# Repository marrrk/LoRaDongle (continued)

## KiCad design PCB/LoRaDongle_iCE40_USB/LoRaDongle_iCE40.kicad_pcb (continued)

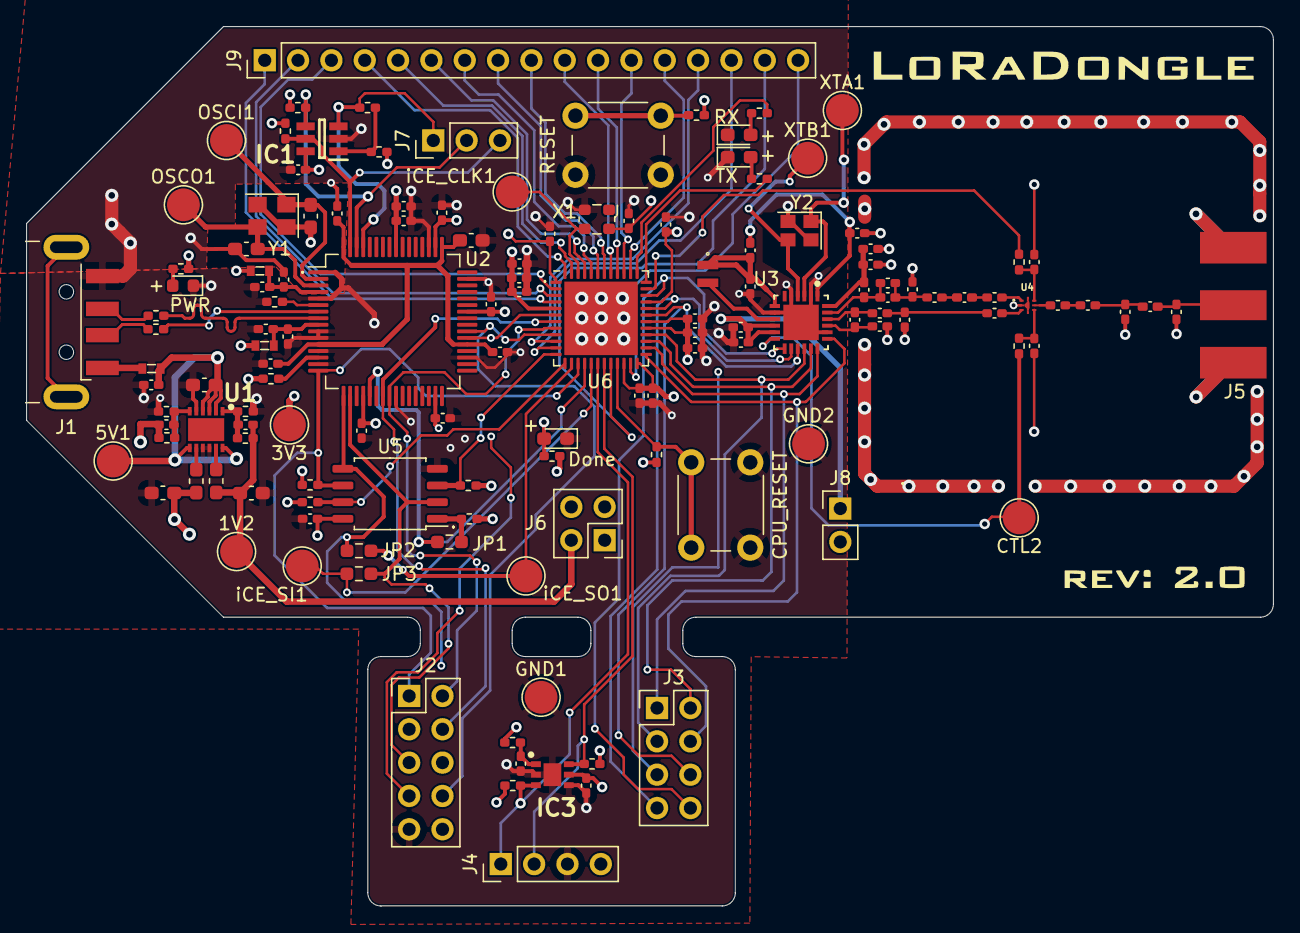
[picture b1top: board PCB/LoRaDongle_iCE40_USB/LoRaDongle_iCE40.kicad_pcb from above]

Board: 4 copper layers, 95.0 x 67.0 mm, 140 parts (1 on the bottom side), 97 nets.

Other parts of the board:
G1: LOGO; LoRaDongleLogo
G3: LOGO; mark_njoroge

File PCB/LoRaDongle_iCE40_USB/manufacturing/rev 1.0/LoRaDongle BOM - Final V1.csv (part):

Item,Qty,Reference(s),Value,Footprint,Description,Manufacturer,Manufacturer Part Number,Package,Type,Comments
1,11,"C1, C8, C9, C12, C13, C16, C18, C19, C20, C21, C22",0.1uF,Capacitor_SMD:C_0402_1005Metric_Pad0.74x0.62mm_HandSolder,CAP CER 0.1UF 16V X7R 0402,Murata Electronics,GCM155R71C104KA55J,0402,SMD,
2,3,"C2, C4, C6",10uF,Capacitor_SMD:C_0603_1608Metric_Pad1.08x0.95mm_HandSolder,CAP CER 10UF 6.3V X5R 0603,Murata Electronics,GRM188R60J106ME47D,0603,SMD,
3,3,"C3, C5, C47",22pF,Capacitor_SMD:C_0402_1005Metric_Pad0.74x0.62mm_HandSolder,CAP CER 22PF 50V C0G/NP0 0402,Murata Electronics,GRM1555C1H220FA01D,0402,SMD,
4,3,"C7, C11, C17",4.7uF,Capacitor_SMD:C_0402_1005Metric_Pad0.74x0.62mm_HandSolder,CAP CER 4.7UF 6.3V X6S 0402,Murata Electronics,GRM155C80J475MEAAD,0402,SMD,
5,2,"C10, C35",10nF,Capacitor_SMD:C_0402_1005Metric_Pad0.74x0.62mm_HandSolder,CAP CER 10000PF 50V X7R 0402,Murata Electronics,GRM155R71H103KA88J,0402,SMD,
6,2,"C14, C15",27pF,Capacitor_SMD:C_0603_1608Metric_Pad1.08x0.95mm_HandSolder,CAP CER 27PF 50V C0G/NP0 0603,Murata Electronics,GRM1885C1H270JA01D,0603,SMD,
7,10,"C23, C24, C25, C26, C27, C29, C30, C31, C32, C33",100nF,Capacitor_SMD:C_0402_1005Metric_Pad0.74x0.62mm_HandSolder,CAP CER 0.1UF 16V X7R 0402,Murata Electronics,GRM155R71C104KA88D,0402,SMD,
8,2,"C28, C34",1uF,Capacitor_SMD:C_0402_1005Metric_Pad0.74x0.62mm_HandSolder,CAP CER 1UF 6.3V X7R 0402,Murata Electronics,GRM155R70J105MA12D,0402,SMD,
9,2,"C36, C37",1.8pF,Capacitor_SMD:C_0402_1005Metric_Pad0.74x0.62mm_HandSolder,CAP CER 1.8PF 50V C0G/NP0 0402,Murata Electronics,GRM1555C1H1R8WA01D,0402,SMD,
10,1,C38,1pF,Capacitor_SMD:C_0402_1005Metric_Pad0.74x0.62mm_HandSolder,CAP CER 1PF 50V C0G/NP0 0402,Murata Electronics,GRM1555C1H1R0BA01D,0402,SMD,
11,3,"C39, C40, C44",470pF,Capacitor_SMD:C_0402_1005Metric_Pad0.74x0.62mm_HandSolder,CAP CER 470PF 50V C0G/NP0 0402,Murata Electronics,GRM1555C1H471JA01D,0402,SMD,
12,2,"C41, C43",33pF,Capacitor_SMD:C_0402_1005Metric_Pad0.74x0.62mm_HandSolder,CAP CER 33PF 50V C0G 0402,TDK Corporation,CGA2B2C0G1H330J050BA,0402,SMD,
13,1,C42,470nF,Capacitor_SMD:C_0402_1005Metric_Pad0.74x0.62mm_HandSolder,CAP CER 0.47UF 10V X5R 0402,Murata Electronics,GRM155R61A474KE15D,0402,SMD,
14,1,C45,47nF,Capacitor_SMD:C_0402_1005Metric_Pad0.74x0.62mm_HandSolder,CAP CER 0.047UF 16V X7R 0402,Murata Electronics,GRM155R71C473KA01J,0402,SMD,
15,1,C46,47pF,Capacitor_SMD:C_0402_1005Metric_Pad0.74x0.62mm_HandSolder,CAP CER 47PF 50V C0G/NP0 0402,Murata Electronics,GRM1555C1H470JA01D,0402,SMD,
16,2,"C48, C50",3.3pF,Capacitor_SMD:C_0402_1005Metric_Pad0.74x0.62mm_HandSolder,CAP CER 3.3PF 50V C0G/NP0 0402,Murata Electronics,GJM1555C1H3R3DB01D,0402,SMD,
17,1,C49,3pF,Capacitor_SMD:C_0402_1005Metric_Pad0.74x0.62mm_HandSolder,CAP CER 3PF 50V C0G/NP0 0402,Murata Electronics,GRM1555C1H3R0BA01J,0402,SMD,
18,1,C51,6.8pF,Capacitor_SMD:C_0402_1005Metric_Pad0.74x0.62mm_HandSolder,CAP CER 6.8PF 50V C0G/NP0 0402,Murata Electronics,GRM1555C1H6R8BA01D,0402,SMD,
19,1,C52,12pF,Capacitor_SMD:C_0402_1005Metric_Pad0.74x0.62mm_HandSolder,CAP CER 12PF 50V C0G/NP0 0402,Murata Electronics,GRM1555C1H120JA01J,0402,SMD,
20,1,D1,PWR,LED_SMD:LED_0805_2012Metric_Pad1.15x1.40mm_HandSolder,LED RED CLEAR CHIP SMD,SunLED,XZM2CRK54WA-8,0805,SMD,
21,1,D2,Done,LED_SMD:LED_0603_1608Metric_Pad1.05x0.95mm_HandSolder,LED GREEN CLEAR CHIP SMD,SunLED,XZVG53W-8,0603,SMD,
22,1,D3,TX,LED_SMD:LED_0603_1608Metric_Pad1.05x0.95mm_HandSolder,LED GREEN CLEAR CHIP SMD,SunLED,XZVG53W-8,0603,SMD,
23,1,D4,RX,LED_SMD:LED_0603_1608Metric_Pad1.05x0.95mm_HandSolder,LED GREEN CLEAR CHIP SMD,SunLED,XZVG53W-8,0603,SMD,
24,3,"FB1, FB2, FB3",600R/0.5A,digikey-footprints:0603,FERRITE BEAD 600 OHM 0603 1LN,Murata Electronics North America,BLM18AG601SN1D,0603,SMD,
25,1,IC1,93LC56BT-I_OT,93LC56B-I_OT_KiCad:SOT95P270X145-6N,"2K,128 X 16,Serial EE,SOT23",Microchip,93LC56BT-I/OT,SOT23-6,SMD,
26,1,IC2,ICE40UP5K-UWG30ITR1K,ICE40UP5K-UWG30ITR1K_KiCad:BGA30C40P5X6_211X254X60,"FPGA - Field Programmable Gate Array iCE40-UltraPlus, 5280 LUTs, 1.2V",Lattice Semiconductor,ICE40UP5K-UWG30ITR1K,"30-UFBGA, WLCSP",SMD,
27,1,IC3,N25Q032A13ESC40F,N25Q032A13ESC40F:SOIC127P600X175-8N,FLASH - NOR Memory IC 32Mb (8M x 4) SPI 108MHz  8-SO,"Alliance Memory, Inc.",N25Q032A13ESC40F,8-SOIC,SMD,
28,1,J1,USB_A,Connector_USB:USB_A_CNCTech_1001-011-01101_Horizontal,"USB A 2.0, R/A, SMT, PLUG",Adam Tech,USB-AP-S-RA-SMT,Plug,SMD - Through Hole,
29,1,J2,Conn_01x08,Connector_PinHeader_2.54mm:PinHeader_2x04_P2.54mm_Vertical,2x04 Male Header,-,-,-,Through Hole,
30,2,"J3, J9",Conn_02x02_Top_Bottom,Connector_PinHeader_2.54mm:PinHeader_2x02_P2.54mm_Vertical,2x02 Male Header,-,-,-,Through Hole,
31,1,J4,Jumper,Connector_PinHeader_2.54mm:PinHeader_1x03_P2.54mm_Vertical,1x03 Male Header,-,-,-,Through Hole,
32,1,J5,142-0701-801,digikey-footprints:RF_SMA_BoardEdge_142-0701-801,CONN SMA JACK STR 50OHM EDGE MNT,Cinch Connectivity Solutions Johnson,142-0701-801,Edge Connector,SMD,
33,1,J6,Conn_01x06,Connector_PinHeader_2.54mm:PinHeader_1x06_P2.54mm_Vertical,1x06 Male Header,-,-,-,Through Hole,
34,1,J7,Jumper_NC_Small,Connector_PinHeader_2.54mm:PinHeader_1x02_P2.54mm_Vertical,1x02 Male Header,-,-,-,Through Hole,
35,1,J8,Jumper,Connector_PinHeader_2.54mm:PinHeader_1x02_P2.54mm_Vertical,1x02 Male Header,-,-,-,Through Hole,
36,1,J10,Jumper_2_Open,Connector_PinHeader_2.54mm:PinHeader_1x02_P2.54mm_Vertical,1x02 Male Header,-,-,-,Through Hole,
37,2,"L1, L2",2.2uH,Inductor_SMD:L_0603_1608Metric_Pad1.05x0.95mm_HandSolder,FIXED IND 2.2UH 1.2A 292MOHM SMD,Taiyo Yuden,MCHK1608T2R2MKN,0603,SMD,
38,2,"L3, L6",47nH,Inductor_SMD:L_0402_1005Metric_Pad0.77x0.64mm_HandSolder,FIXED IND 47NH 210MA 1.08OHM SMD,Murata Electronics,LQW15AN47NJ00D,0402,SMD,
39,1,L4,18nH,Inductor_SMD:L_0402_1005Metric_Pad0.77x0.64mm_HandSolder,FIXED IND 18NH 370MA 270MOHM SMD,Murata Electronics,LQW15AN18NH00D,0402,SMD,
40,1,L5,15uH,KiCad_VLS201610CX-150M-1:VLS2016,FIXED IND 15UH 540MA 1.258OHM SM,TDK,VLS201610CX-150M-1,2016,SMD,
41,2,"L7, L9",9.1nH,Inductor_SMD:L_0402_1005Metric_Pad0.77x0.64mm_HandSolder,FIXED IND 9.1NH 540MA 140MOHM SM,Murata Electronics,LQW15AN9N1H00D,0402,SMD,
42,1,L8,2.7nH,Inductor_SMD:L_0402_1005Metric_Pad0.77x0.64mm_HandSolder,FIXED IND 2.7NH 850MA 50MOHM SMD,Murata Electronics,LQW15AN2N7C00D,0402,SMD,
43,2,"R1, R2",10R,Resistor_SMD:R_0402_1005Metric_Pad0.72x0.64mm_HandSolder,RES 10 OHM 1% 1/16W 0402,Stackpole Electronics Inc,RMCF0402FT10R0,0402,SMD,
44,5,"R3, R18, R19, R20, R21",100R,Resistor_SMD:R_0402_1005Metric_Pad0.72x0.64mm_HandSolder,RES 100 OHM 1% 1/16W 0402,Stackpole Electronics Inc,RMCF0402FT100R,0402,SMD,
45,1,R4,453K,Resistor_SMD:R_0402_1005Metric_Pad0.72x0.64mm_HandSolder,RES 453K OHM 1% 1/16W 0402,Stackpole Electronics Inc,RMCF0402FT453K,0402,SMD,
46,3,"R5, R6, R7",100K,Resistor_SMD:R_0402_1005Metric_Pad0.72x0.64mm_HandSolder,RES 100K OHM 5% 1/16W 0402,Stackpole Electronics Inc,RMCF0402JT100K,0402,SMD,
47,7,"R8, R10, R13, R14, R15, R16, R17",10K,Resistor_SMD:R_0402_1005Metric_Pad0.72x0.64mm_HandSolder,RES 10K OHM 1% 1/16W 0402,Stackpole Electronics Inc,RMCF0402FT10K0,0402,SMD,
48,1,R9,2K,Resistor_SMD:R_0402_1005Metric_Pad0.72x0.64mm_HandSolder,RES 2K OHM 1% 1/16W 0402,Stackpole Electronics Inc,RMCF0402FT2K00,0402,SMD,
49,1,R11,12K,Resistor_SMD:R_0402_1005Metric_Pad0.72x0.64mm_HandSolder,RES 10K OHM 1% 1/16W 0402,Stackpole Electronics Inc,RMCF0402FT12K0,0402,SMD,
50,1,R12,4K7,Resistor_SMD:R_0402_1005Metric_Pad0.72x0.64mm_HandSolder,RES 10K OHM 1% 1/16W 0402,Stackpole Electronics Inc,RMCF0402JT4K70,0402,SMD,
51,1,SW1,SW_Push,Button_Switch_THT:SW_PUSH_6mm_H5mm,Push Button Switch,,,,Through Hole,
52,1,U1,RP550K001A-TR,RP550K001A-TR_KiCad:SON50P270X300X60-13N,BUCK DC/DC CONVERTER DUAL OUTPUT,Nisshinbo Micro Devices Inc.,RP550K001A-TR,DFN(PLP)2730-12,SMD,
53,1,U2,FT232H,Package_QFP:LQFP-48_7x7mm_P0.5mm,IC HS USB TO UART/FIFO 48LQFP,"FTDI, Future Technology Devices International Ltd",FT232HL,LQFP-48,SMD,"If out of stock, do not populate"
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
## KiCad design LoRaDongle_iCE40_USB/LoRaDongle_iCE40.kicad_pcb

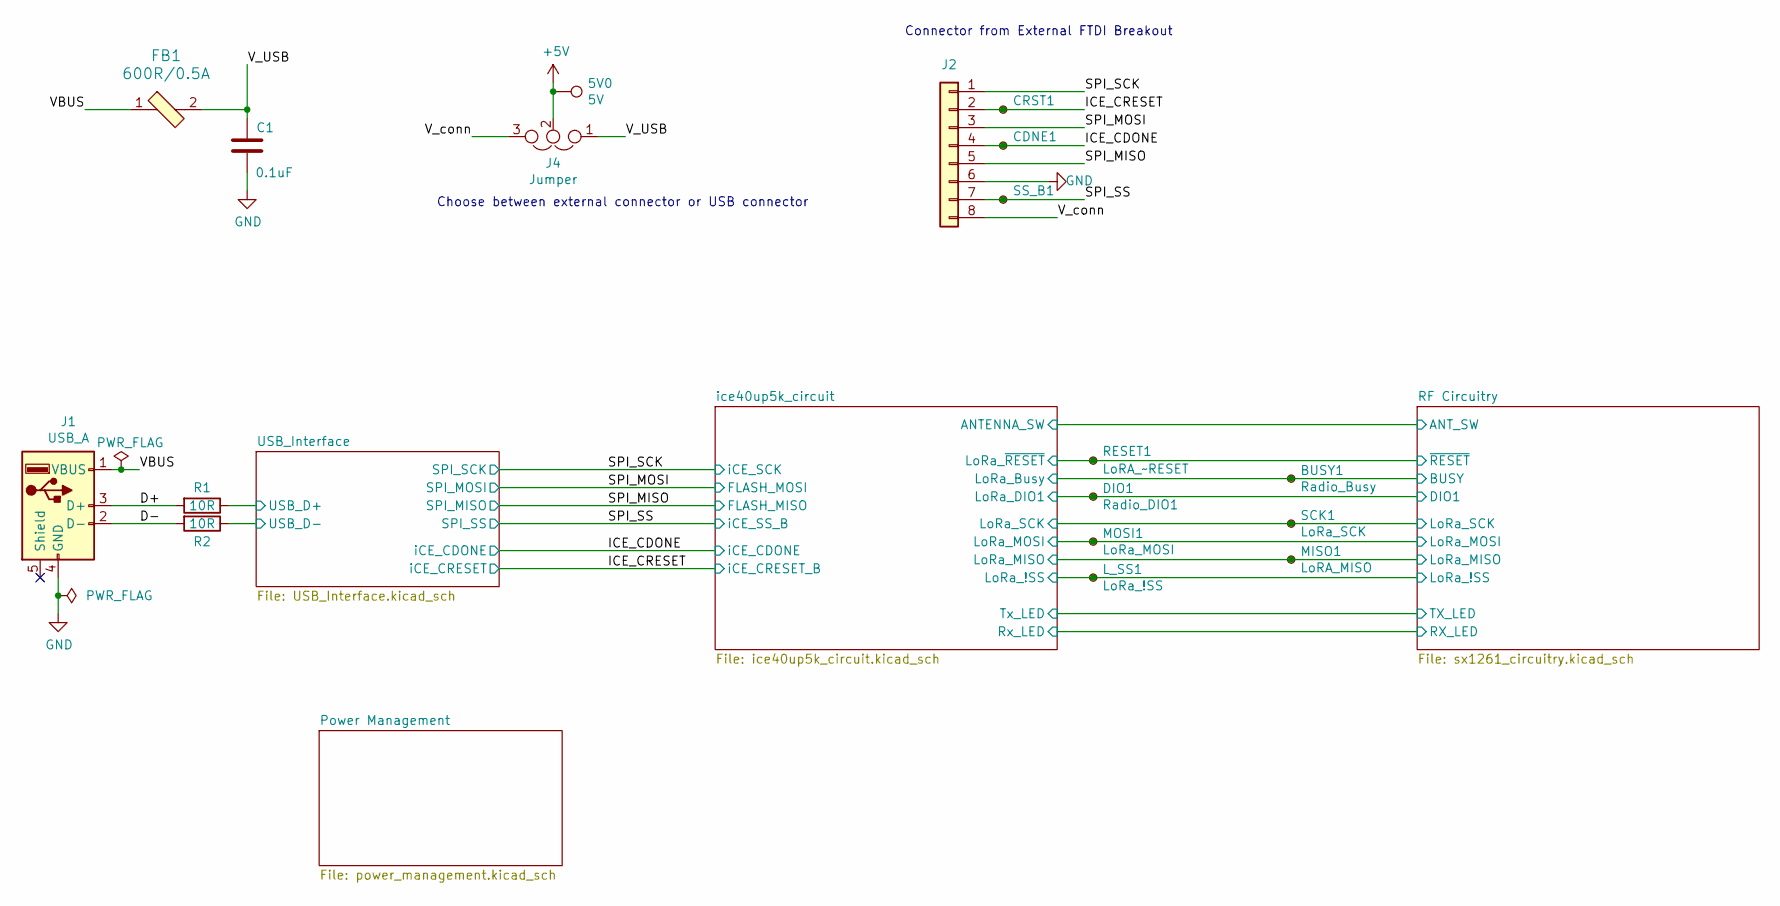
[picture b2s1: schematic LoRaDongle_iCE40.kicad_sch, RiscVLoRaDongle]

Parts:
5V0: 5V; TestPoint_Pad_D1.0mm
BUSY1: Radio_Busy; TestPoint_Pad_D1.0mm
C1: 0.1uF; C_0402_1005Metric_Pad0.74x0.62mm_HandSolder; Part Number GCM155R71C104KA55J
CDNE1: iCE_CDONE; TestPoint_Pad_D1.0mm
CRST1: iCE_CRESET; TestPoint_Pad_D1.0mm
DIO1: Radio_DIO1; TestPoint_Pad_D1.0mm
FB1: 600R/0.5A; 0603; MPN BLM18AG601SN1D; Digi-Key_PN 490-1014-1-ND
J1: USB_A; USB_A_CNCTech_1001-011-01101_Horizontal; Manufacturer Part Number USB-AP-S-RA-SMT
J2: Conn_01x08; PinHeader_2x04_P2.54mm_Vertical
J4: Jumper; PinHeader_1x03_P2.54mm_Vertical
L_SS1: LoRa_!SS; TestPoint_Pad_D1.0mm
MISO1: LoRA_MISO; TestPoint_Pad_D1.0mm
MOSI1: LoRa_MOSI; TestPoint_Pad_D1.0mm
R1, R2: 10R; R_0402_1005Metric_Pad0.72x0.64mm_HandSolder; Manufacturer Part Number RMCF0402FT10R0
RESET1: LoRA_~RESET; TestPoint_Pad_D1.0mm
SCK1: LoRa_SCK; TestPoint_Pad_D1.0mm
SS_B1: iCE_SS_B; TestPoint_Pad_D1.0mm

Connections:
+5V: 5V0.1, J4.2; also elsewhere on the board
/D+: J1.3 (D+), R1.2
/D-: J1.2 (D-), R2.2
/ICE_CDONE: CDNE1.1, J2.4; also elsewhere on the board
/ICE_CRESET: CRST1.1, J2.2; also elsewhere on the board
/RF Circuitry/BUSY: BUSY1.1; also elsewhere on the board
/RF Circuitry/DIO1: DIO1.1; also elsewhere on the board
/RF Circuitry/LoRa_!SS: L_SS1.1; also elsewhere on the board
/RF Circuitry/LoRa_MISO: MISO1.1; also elsewhere on the board
/RF Circuitry/LoRa_MOSI: MOSI1.1; also elsewhere on the board
/RF Circuitry/~RESET: RESET1.1; also elsewhere on the board
/SPI_MISO: J2.5; also elsewhere on the board
/SPI_MOSI: J2.3; also elsewhere on the board
/SPI_SCK: J2.1, SCK1.1; also elsewhere on the board
/SPI_SS: J2.7, SS_B1.1; also elsewhere on the board
/USB_Interface/USB_D+: R1.1; also elsewhere on the board
/USB_Interface/USB_D-: R2.1; also elsewhere on the board
/VBUS: FB1.1, J1.1 (VBUS)
/V_USB: C1.2, FB1.2, J4.1
/V_conn: J2.8, J4.3
GND: C1.1, J1.4 (GND), J2.6; also elsewhere on the board

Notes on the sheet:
Choose between external connector or USB connector
Connector from External FTDI Breakout

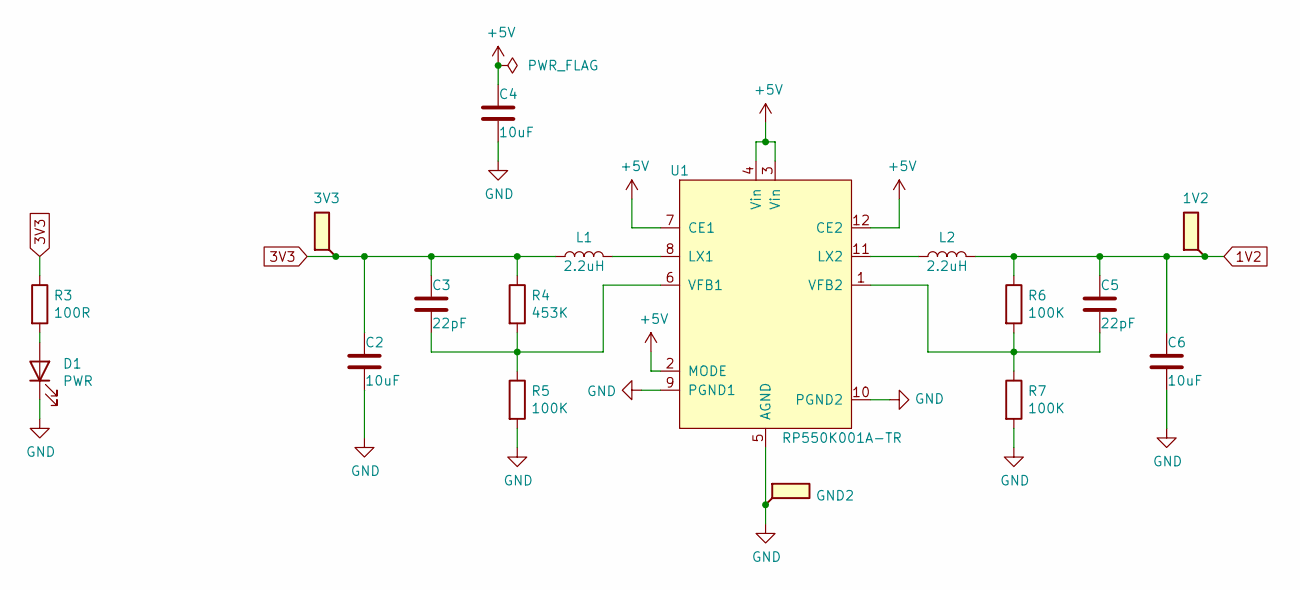
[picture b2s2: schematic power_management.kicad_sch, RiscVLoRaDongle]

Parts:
1V2: 1.2V; TestPoint_Pad_D1.0mm
3V3: 3.3V; TestPoint_Pad_D1.0mm
C2, C4, C6: 10uF; C_0603_1608Metric_Pad1.08x0.95mm_HandSolder; Part Number GRM188R61E106KA73J
C3, C5: 22pF; C_0402_1005Metric_Pad0.74x0.62mm_HandSolder; Part Number GRM1555C1H220FA01D
D1: PWR; LED_0805_2012Metric_Pad1.15x1.40mm_HandSolder; Manufacturer Part Number XZM2CRK54WA-8
GND2: GND; TestPoint_Pad_D1.0mm
L1, L2: 2.2uH; L_0603_1608Metric_Pad1.05x0.95mm_HandSolder; Part Number MCHK1608T2R2MKN
R3: 100R; R_0402_1005Metric_Pad0.72x0.64mm_HandSolder; Manufacturer Part Number RMCF0402FT100R
R4: 453K; R_0402_1005Metric_Pad0.72x0.64mm_HandSolder; Manufacturer Part Number RMCF0402FT453K
R5, R6, R7: 100K; R_0402_1005Metric_Pad0.72x0.64mm_HandSolder; Manufacturer Part Number RMCF0402JT100K
U1: RP550K001A-TR; SON50P270X300X60-13N; Manufacturer Part Number RP550K001A-TR

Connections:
1V2: 1V2.1, C5.2, C6.2, L2.2, R6.1; also elsewhere on the board
3V3: 3V3.1, C2.2, C3.2, L1.1, R3.1, R4.1; also elsewhere on the board
+5V: C4.2, U1.2 (MODE), U1.3 (Vin), U1.4 (Vin), U1.7 (CE1), U1.12 (CE2); also elsewhere on the board
GND: C2.1, C4.1, C6.1, D1.1 (K), GND2.1, R5.2, R7.2, U1.5 (AGND), U1.9 (PGND1), U1.10 (PGND2); also elsewhere on the board
unnamed: C3.1, R4.2, R5.1, U1.6 (VFB1)
unnamed: C5.1, R6.2, R7.1, U1.1 (VFB2)
unnamed: D1.2 (A), R3.2
unnamed: L1.2, U1.8 (LX1)
unnamed: L2.1, U1.11 (LX2)

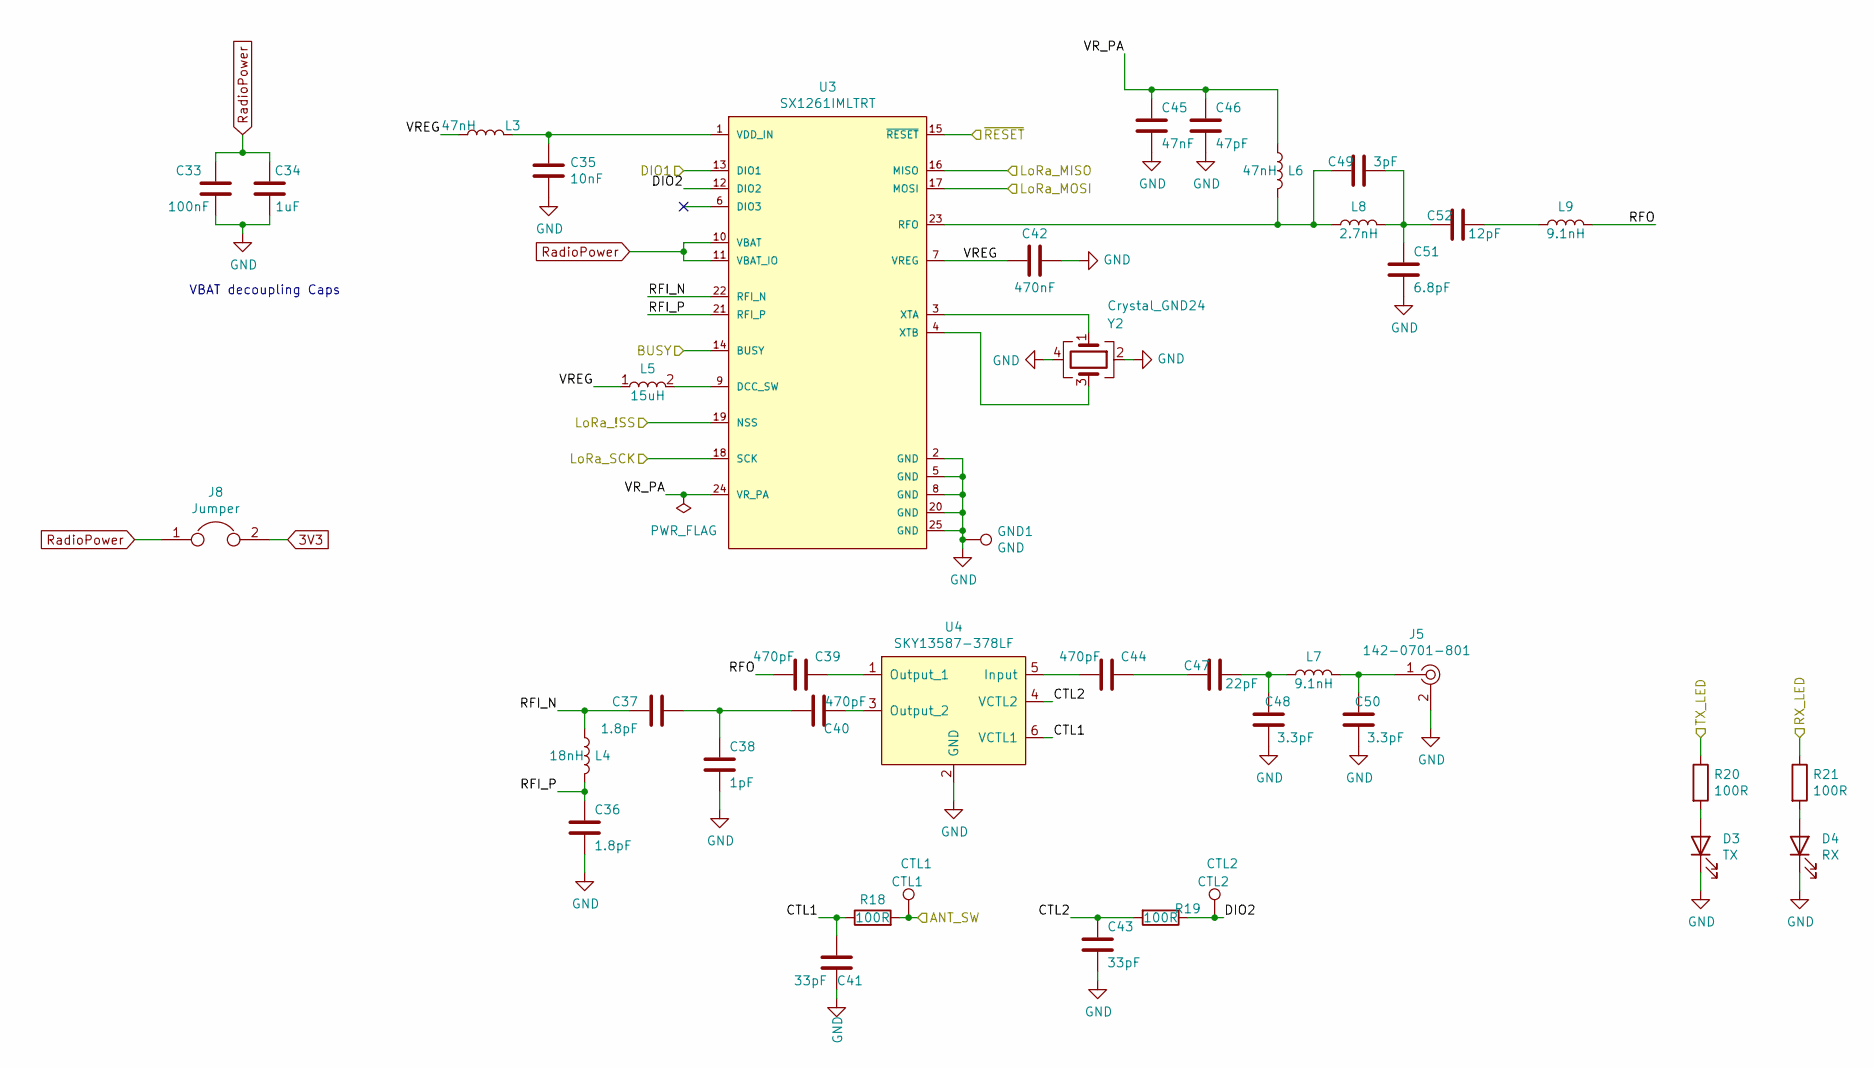
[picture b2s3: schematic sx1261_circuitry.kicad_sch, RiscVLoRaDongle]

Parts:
C33: 100nF; C_0402_1005Metric_Pad0.74x0.62mm_HandSolder; Part Number GRM155R71C104KA88D
C34: 1uF; C_0402_1005Metric_Pad0.74x0.62mm_HandSolder; Manufacturer Part Number GRM155R70J105MA12D
C35: 10nF; C_0402_1005Metric_Pad0.74x0.62mm_HandSolder; Part Number GRM155R71H103KA88J
C36, C37: 1.8pF; C_0402_1005Metric_Pad0.74x0.62mm_HandSolder; part Number GRM1555C1H1R8WA01D
C38: 1pF; C_0402_1005Metric_Pad0.74x0.62mm_HandSolder; part Number GRM1555C1H1R0BA01D
C39, C40, C44: 470pF; C_0402_1005Metric_Pad0.74x0.62mm_HandSolder; Part Number GRM1555C1H471JA01D
C41, C43: 33pF; C_0402_1005Metric_Pad0.74x0.62mm_HandSolder; Part Number CGA2B2C0G1H330J050BA
C42: 470nF; C_0402_1005Metric_Pad0.74x0.62mm_HandSolder; Part Number GRM155R61A474KE15D
C45: 47nF; C_0402_1005Metric_Pad0.74x0.62mm_HandSolder; Part Number GRM155R71C473KA01J
C46: 47pF; C_0402_1005Metric_Pad0.74x0.62mm_HandSolder; Part Number GRM1555C1H470JA01D
C47: 22pF; C_0402_1005Metric_Pad0.74x0.62mm_HandSolder; Part Number GRM1555C1H220JA01D
C48, C50: 3.3pF; C_0402_1005Metric_Pad0.74x0.62mm_HandSolder; Part Number GJM1555C1H3R3DB01D
C49: 3pF; C_0402_1005Metric_Pad0.74x0.62mm_HandSolder; Part Number GRM1555C1H3R0BA01J
C51: 6.8pF; C_0402_1005Metric_Pad0.74x0.62mm_HandSolder; Part Number GRM1555C1H6R8BA01D
C52: 12pF; C_0402_1005Metric_Pad0.74x0.62mm_HandSolder; Part Number GRM1555C1H120JA01J
CTL1: CTL1; TestPoint_Pad_D1.0mm
CTL2: CTL2; TestPoint_Pad_D1.0mm
D3: TX; LED_0603_1608Metric_Pad1.05x0.95mm_HandSolder; Manufacturer Part Number XZVG53W-8
D4: RX; LED_0603_1608Metric_Pad1.05x0.95mm_HandSolder; Manufacturer Part Number XZVG53W-8
GND1: GND; TestPoint_Pad_D1.0mm
J5: 142-0701-801; RF_SMA_BoardEdge_142-0701-801; MPN 142-0701-801; Digi-Key_PN J502-ND
J8: Jumper; PinHeader_1x02_P2.54mm_Vertical
L3: 47nH; L_0402_1005Metric_Pad0.77x0.64mm_HandSolder; PartNumber LQW15AN47NJ00D
L4: 18nH; L_0402_1005Metric_Pad0.77x0.64mm_HandSolder; part Number LQW15AN18NH00D
L5: 15uH; VLS2016; Manufacturer_Part_Number VLS201610CX-150M-1; Mouser Part Number 810-VLS201610CX150M1
L6: 47nH; L_0402_1005Metric_Pad0.77x0.64mm_HandSolder; Part Number LQW15AN47NJ00D
L7, L9: 9.1nH; L_0402_1005Metric_Pad0.77x0.64mm_HandSolder; Part Number LQW15AN9N1H00D
L8: 2.7nH; L_0402_1005Metric_Pad0.77x0.64mm_HandSolder; Part Number LQW15AN2N7C00D
R18, R19, R20, R21: 100R; R_0402_1005Metric_Pad0.72x0.64mm_HandSolder; Manufacturer Part Number RMCF0402FT100R
U3: SX1261IMLTRT; Semtech-QFN24-0-0-0; mouser part number 947-SX1261IMLTRT; digikey description TXRX LORA SUB-GHZ 15DBM 24MLPQ
U4: SKY13587-378LF; SW_SKYA21012; Manufacturer Part Number SKY13587-378LF
Y2: Crystal_GND24; Crystal_SMD_2520-4Pin_2.5x2.0mm; Part Number ECS-320-10-36B-CKM-TR

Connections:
3V3: J8.2; also elsewhere on the board
/RF Circuitry/ANT_SW: CTL1.1, R18.2; also elsewhere on the board
/RF Circuitry/BUSY: U3.14 (BUSY); also elsewhere on the board
/RF Circuitry/CTL1: C41.2, R18.1, U4.6 (VCTL1)
/RF Circuitry/CTL2: C43.1, R19.2, U4.4 (VCTL2)
/RF Circuitry/DIO1: U3.13 (DIO1); also elsewhere on the board
/RF Circuitry/DIO2: CTL2.1, R19.1, U3.12 (DIO2)
/RF Circuitry/LoRa_!SS: U3.19 (NSS); also elsewhere on the board
/RF Circuitry/LoRa_MISO: U3.16 (MISO); also elsewhere on the board
/RF Circuitry/LoRa_MOSI: U3.17 (MOSI); also elsewhere on the board
/RF Circuitry/RFI_N: C37.1, L4.1, U3.22 (RFI_N)
/RF Circuitry/RFI_P: C36.1, L4.2, U3.21 (RFI_P)
/RF Circuitry/RFO: C39.1, L9.2
/RF Circuitry/RX_LED: R21.1; also elsewhere on the board
/RF Circuitry/TX_LED: R20.1; also elsewhere on the board
/RF Circuitry/VREG: C42.2, L3.1, L5.1, U3.7 (VREG)
/RF Circuitry/VR_PA: C45.1, C46.1, L6.1, U3.24 (VR_PA)
/RF Circuitry/~RESET: U3.15 (~RESET); also elsewhere on the board
/SPI_SCK: U3.18 (SCK); also elsewhere on the board
GND: C33.1, C34.1, C35.2, C36.2, C38.2, C41.1, C42.1, C43.2, C45.2, C46.2, C48.1, C50.1, C51.2, D3.1 (K), D4.1 (K), GND1.1, J5.2, U3.2 (GND), U3.5 (GND), U3.8 (GND), U3.20 (GND), U3.25 (GND), U4.2 (GND), Y2.2, Y2.4; also elsewhere on the board
unnamed: C35.1, L3.2, U3.1 (VDD_IN)
unnamed: C37.2, C38.1, C40.1
unnamed: C39.2, U4.1 (Output_1)
unnamed: C40.2, U4.3 (Output_2)
unnamed: C44.1, U4.5 (Input)
unnamed: C44.2, C47.2
unnamed: C47.1, C48.2, L7.1
unnamed: C49.1, C51.1, C52.2, L8.2
unnamed: C49.2, L6.2, L8.1, U3.23 (RFO)
unnamed: C50.2, J5.1, L7.2
unnamed: C52.1, L9.1
unnamed: D3.2 (A), R20.2
unnamed: D4.2 (A), R21.2
unnamed: L5.2, U3.9 (DCC_SW)
unnamed: U3.3 (XTA), Y2.1
unnamed: U3.4 (XTB), Y2.3
RadioPower: C33.2, C34.2, J8.1, U3.10 (VBAT), U3.11 (VBAT_IO)

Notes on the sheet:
VBAT decoupling Caps

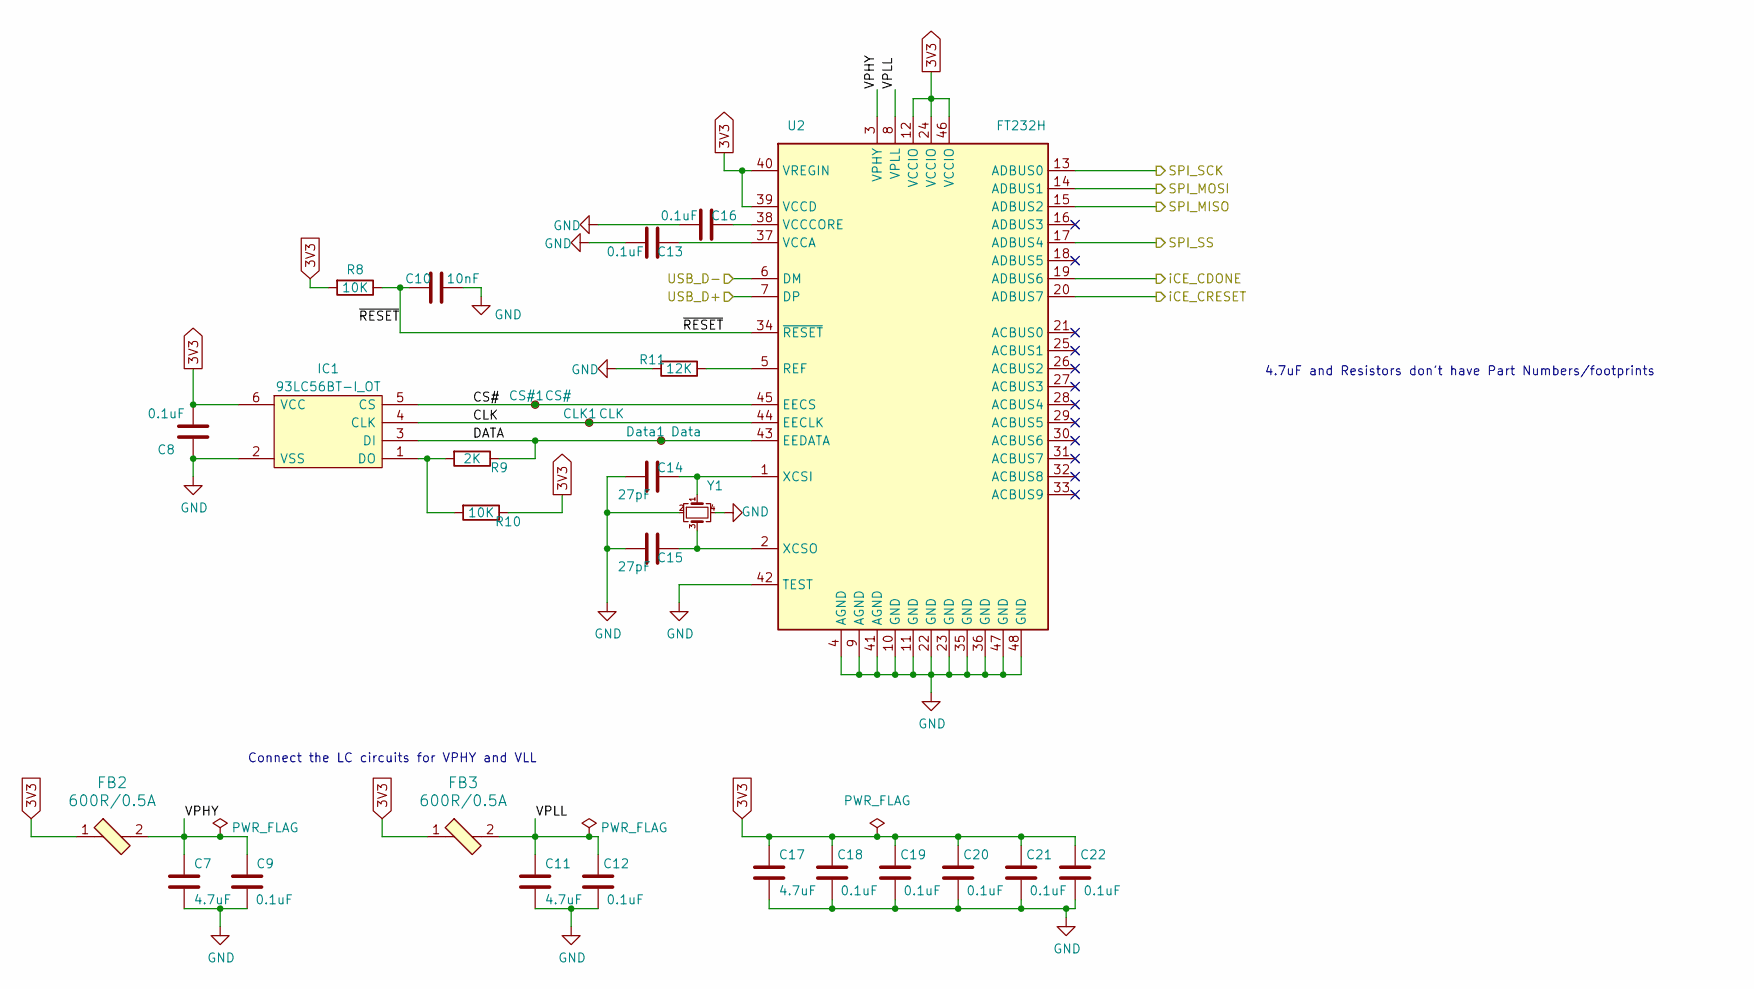
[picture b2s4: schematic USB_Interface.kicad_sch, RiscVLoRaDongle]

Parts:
C7, C11, C17: 4.7uF; C_0402_1005Metric_Pad0.74x0.62mm_HandSolder; Part Number GRM155C80J475MEAAD
C8, C9, C12, C13, C16, C18, C19, C20, C21, C22: 0.1uF; C_0402_1005Metric_Pad0.74x0.62mm_HandSolder; Part Number GCM155R71C104KA55J
C10: 10nF; C_0402_1005Metric_Pad0.74x0.62mm_HandSolder; Part Number GRM155R71H103KA88J
C14, C15: 27pF; C_0603_1608Metric_Pad1.08x0.95mm_HandSolder; Manufacturer Part Number GRM1885C1H270JA01D
CLK1: CLK; TestPoint_Pad_D1.0mm
CS#1: CS#; TestPoint_Pad_D1.0mm
Data1: Data; TestPoint_Pad_D1.0mm
FB2, FB3: 600R/0.5A; 0603; MPN BLM18AG601SN1D; Digi-Key_PN 490-1014-1-ND
IC1: 93LC56BT-I_OT; SOT95P270X145-6N; Manufacturer_Part_Number 93LC56BT-I/OT; Mouser Part Number 579-93LC56BT-I/OT
R8, R10: 10K; R_0402_1005Metric_Pad0.72x0.64mm_HandSolder; Manufacturer Part Number RMCF0402FT10K0
R9: 2K; R_0402_1005Metric_Pad0.72x0.64mm_HandSolder; Manufacturer Part Number RMCF0402FT2K00
R11: 12K; R_0402_1005Metric_Pad0.72x0.64mm_HandSolder; Manufacturer Part Number RMCF0402FT12K0
U2: FT232H; LQFP-48_7x7mm_P0.5mm; Manufacturer Part Number FT232HL
Y1: Crystal_GND24_Small; Crystal_SMD_3225-4Pin_3.2x2.5mm; Part Number ABM8-12.000MHZ-B2-T

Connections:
3V3: C8.2, C17.1, C18.2, C19.2, C20.2, C21.2, C22.2, FB2.1, FB3.1, IC1.6 (VCC), R8.2, R10.1, U2.12 (VCCIO), U2.24 (VCCIO), U2.39 (VCCD), U2.40 (VREGIN), U2.46 (VCCIO); also elsewhere on the board
/ICE_CDONE: U2.19 (ADBUS6); also elsewhere on the board
/ICE_CRESET: U2.20 (ADBUS7); also elsewhere on the board
/SPI_MISO: U2.15 (ADBUS2); also elsewhere on the board
/SPI_MOSI: U2.14 (ADBUS1); also elsewhere on the board
/SPI_SCK: U2.13 (ADBUS0); also elsewhere on the board
/SPI_SS: U2.17 (ADBUS4); also elsewhere on the board
/USB_Interface/CLK: CLK1.1, IC1.4 (CLK), U2.44 (EECLK)
/USB_Interface/CS#: CS#1.1, IC1.5 (CS), U2.45 (EECS)
/USB_Interface/DATA: Data1.1, IC1.3 (DI), R9.1, U2.43 (EEDATA)
/USB_Interface/USB_D+: U2.7 (DP); also elsewhere on the board
/USB_Interface/USB_D-: U2.6 (DM); also elsewhere on the board
/USB_Interface/VPHY: C7.1, C9.2, FB2.2, U2.3 (VPHY)
/USB_Interface/VPLL: C11.1, C12.2, FB3.2, U2.8 (VPLL)
/USB_Interface/~RESET: C10.2, R8.1, U2.34 (~RESET)
GND: C7.2, C8.1, C9.1, C10.1, C11.2, C12.1, C13.2, C14.2, C15.2, C16.2, C17.2, C18.1, C19.1, C20.1, C21.1, C22.1, IC1.2 (VSS), R11.2, U2.4 (AGND), U2.9 (AGND), U2.10 (GND), U2.11 (GND), U2.22 (GND), U2.23 (GND), U2.35 (GND), U2.36 (GND), U2.41 (AGND), U2.42 (TEST), U2.47 (GND), U2.48 (GND), Y1.2, Y1.4; also elsewhere on the board
unnamed: C13.1, U2.37 (VCCA)
unnamed: C14.1, U2.1 (XCSI), Y1.1
unnamed: C15.1, U2.2 (XCSO), Y1.3
unnamed: C16.1, U2.38 (VCCCORE)
unnamed: IC1.1 (DO), R9.2, R10.2
unnamed: R11.1, U2.5 (REF)

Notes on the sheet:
4.7uF and Resistors don't have Part Numbers/footprints
Connect the LC circuits for VPHY and VLL

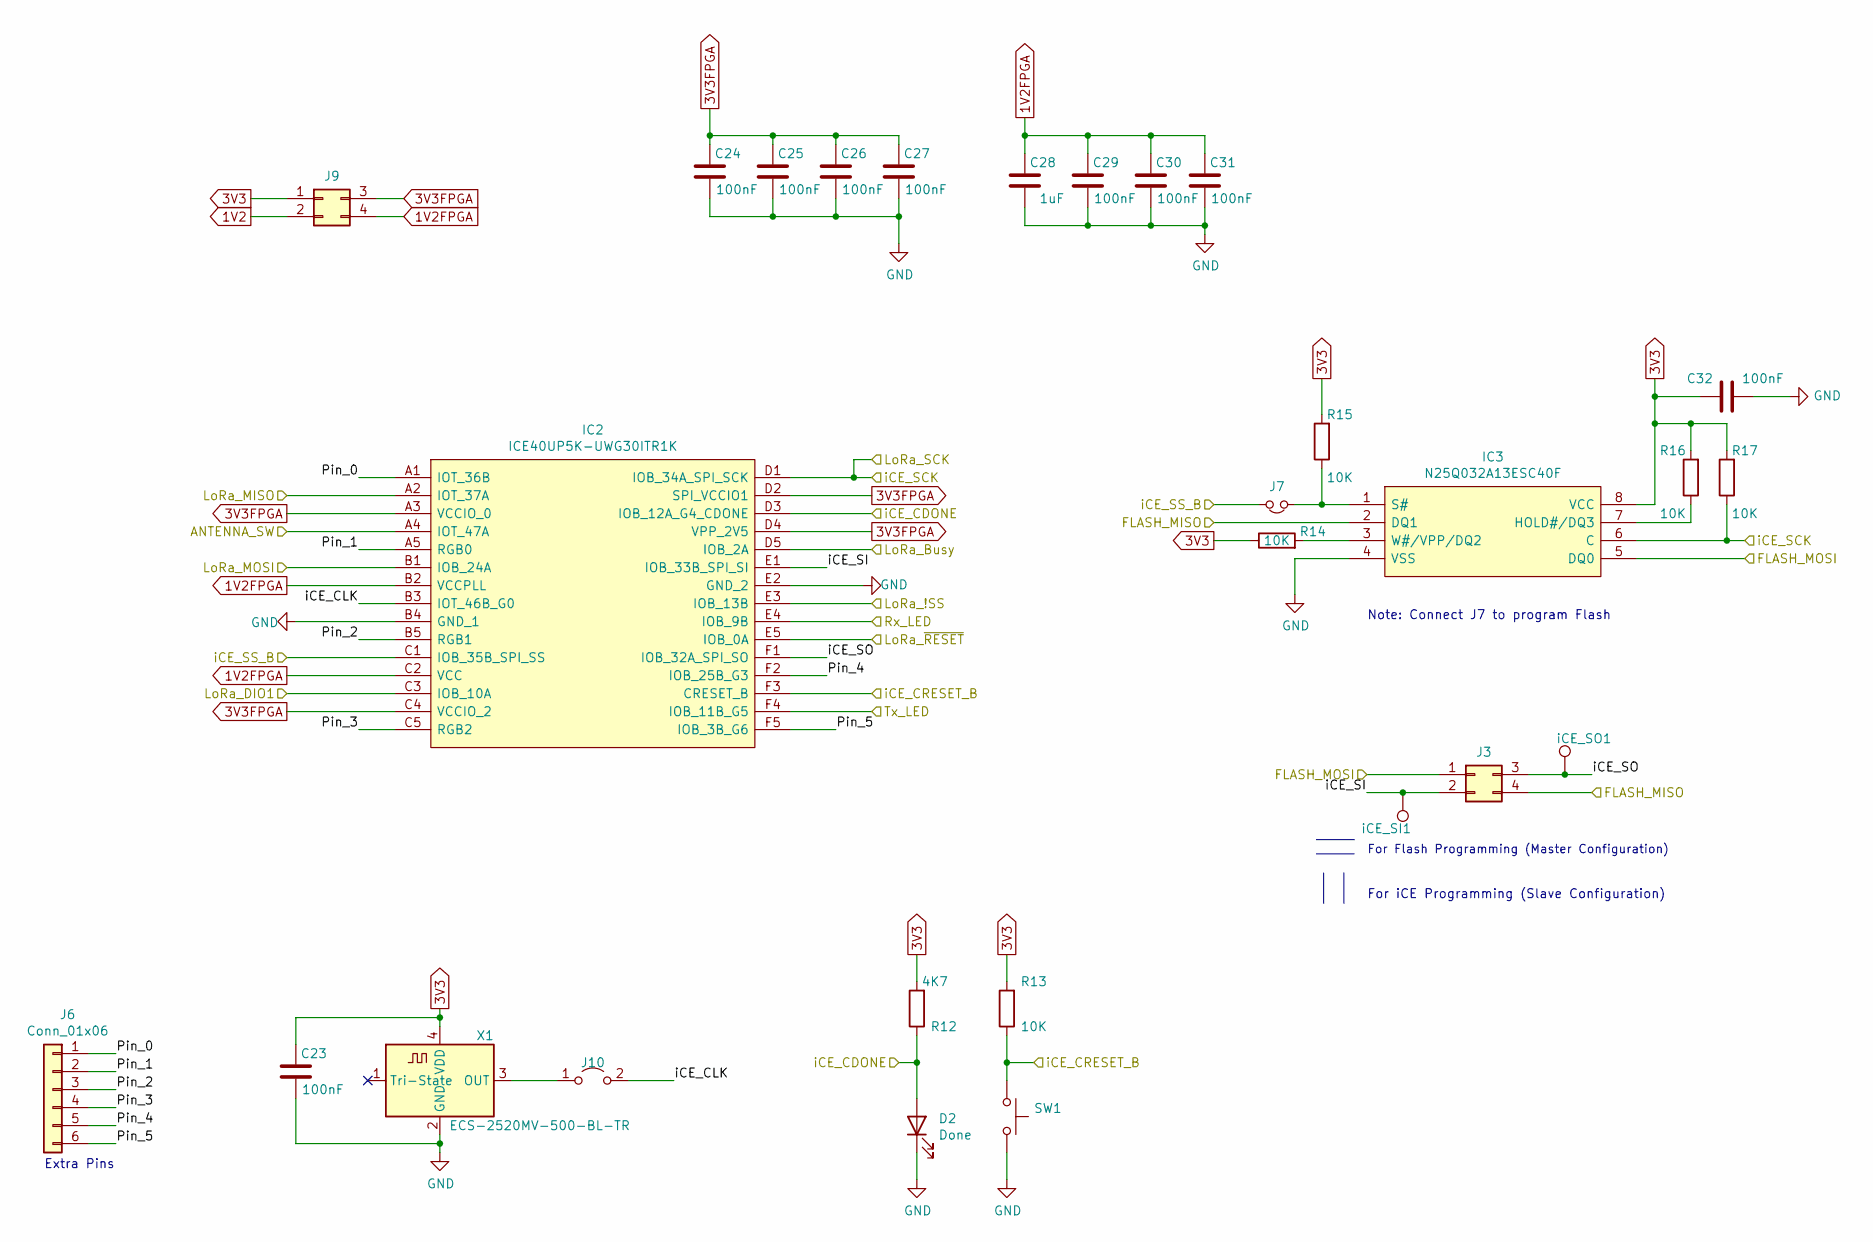
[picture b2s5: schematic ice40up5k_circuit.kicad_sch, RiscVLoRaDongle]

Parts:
C23, C24, C25, C26, C27, C29, C30, C31, C32: 100nF; C_0402_1005Metric_Pad0.74x0.62mm_HandSolder; Part Number GRM155R71C104KA88D
C28: 1uF; C_0402_1005Metric_Pad0.74x0.62mm_HandSolder; Part Number GRM155R70J105MA12D
D2: Done; LED_0603_1608Metric_Pad1.05x0.95mm_HandSolder; Manufacturer Part Number XZVG53W-8
IC2: ICE40UP5K-UWG30ITR1K; BGA30C40P5X6_211X254X60; Manufacturer_Part_Number ICE40UP5K-UWG30ITR1K; Mouser Part Number 842-40UP5KUWG30ITR1K
IC3: N25Q032A13ESC40F; SOIC127P600X175-8N; Manufacturer_Part_Number N25Q032A13ESC40F; Mouser Part Number 913-N25Q032A13ESC40F
J3, J9: Conn_02x02_Top_Bottom; PinHeader_2x02_P2.54mm_Vertical
J6: Conn_01x06; PinHeader_1x06_P2.54mm_Vertical
J7: Jumper_NC_Small; PinHeader_1x02_P2.54mm_Vertical
J10: Jumper_2_Open; PinHeader_1x02_P2.54mm_Vertical
R12: 4K7; R_0402_1005Metric_Pad0.72x0.64mm_HandSolder; Manufacturer Part Number RMCF0402JT4K70
R13, R14, R15, R16, R17: 10K; R_0402_1005Metric_Pad0.72x0.64mm_HandSolder; Manufacturer Part Number RMCF0402FT10K0
SW1: SW_Push; SW_PUSH_6mm_H5mm
X1: ECS-2520MV-500-BL-TR; Oscillator_SMD_ECS_2520MV-xxx-xx-4Pin_2.5x2.0mm; Manufacturer Part Number ECS-2520MV-500-BL-TR
iCE_SI1: iCE_SI; TestPoint_Pad_D1.0mm
iCE_SO1: iCE_SO; TestPoint_Pad_D1.0mm

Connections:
1V2: J9.2; also elsewhere on the board
1V2FPGA: C28.2, C29.2, C30.2, C31.2, IC2.B2 (VCCPLL), IC2.C2 (VCC), J9.4
3V3: C23.2, C32.2, IC3.8 (VCC), J9.1, R12.2, R13.2, R14.1, R15.2, R16.2, R17.2, X1.4 (VDD); also elsewhere on the board
3V3FPGA: C24.2, C25.2, C26.2, C27.2, IC2.A3 (VCCIO_0), IC2.C4 (VCCIO_2), IC2.D2 (SPI_VCCIO1), IC2.D4 (VPP_2V5), J9.3
/ICE_CDONE: D2.2 (A), IC2.D3 (IOB_12A_G4_CDONE), R12.1; also elsewhere on the board
/ICE_CRESET: IC2.F3 (CRESET_B), R13.1, SW1.1; also elsewhere on the board
/RF Circuitry/ANT_SW: IC2.A4 (IOT_47A); also elsewhere on the board
/RF Circuitry/BUSY: IC2.D5 (IOB_2A); also elsewhere on the board
/RF Circuitry/DIO1: IC2.C3 (IOB_10A); also elsewhere on the board
/RF Circuitry/LoRa_!SS: IC2.E3 (IOB_13B); also elsewhere on the board
/RF Circuitry/LoRa_MISO: IC2.A2 (IOT_37A); also elsewhere on the board
/RF Circuitry/LoRa_MOSI: IC2.B1 (IOB_24A); also elsewhere on the board
/RF Circuitry/RX_LED: IC2.E4 (IOB_9B); also elsewhere on the board
/RF Circuitry/TX_LED: IC2.F4 (IOB_11B_G5); also elsewhere on the board
/RF Circuitry/~RESET: IC2.E5 (IOB_0A); also elsewhere on the board
/SPI_MISO: IC3.2 (DQ1), J3.4; also elsewhere on the board
/SPI_MOSI: IC3.5 (DQ0), J3.1; also elsewhere on the board
/SPI_SCK: IC2.D1 (IOB_34A_SPI_SCK), IC3.6 (C), R17.1; also elsewhere on the board
/SPI_SS: IC2.C1 (IOB_35B_SPI_SS), J7.2; also elsewhere on the board
/ice40up5k_circuit/Pin_0: IC2.A1 (IOT_36B), J6.1
/ice40up5k_circuit/Pin_1: IC2.A5 (RGB0), J6.2
/ice40up5k_circuit/Pin_2: IC2.B5 (RGB1), J6.3
/ice40up5k_circuit/Pin_3: IC2.C5 (RGB2), J6.4
/ice40up5k_circuit/Pin_4: IC2.F2 (IOB_25B_G3), J6.5
/ice40up5k_circuit/Pin_5: IC2.F5 (IOB_3B_G6), J6.6
/ice40up5k_circuit/iCE_CLK: IC2.B3 (IOT_46B_G0), J10.2 (B)
/ice40up5k_circuit/iCE_SI: IC2.E1 (IOB_33B_SPI_SI), J3.2, iCE_SI1.1
/ice40up5k_circuit/iCE_SO: IC2.F1 (IOB_32A_SPI_SO), J3.3, iCE_SO1.1
GND: C23.1, C24.1, C25.1, C26.1, C27.1, C28.1, C29.1, C30.1, C31.1, C32.1, D2.1 (K), IC2.B4 (GND_1), IC2.E2 (GND_2), IC3.4 (VSS), SW1.2, X1.2 (GND); also elsewhere on the board
unnamed: IC3.1 (S#), J7.1, R15.1
unnamed: IC3.3 (W#/VPP/DQ2), R14.2
unnamed: IC3.7 (HOLD#/DQ3), R16.1
unnamed: J10.1 (A), X1.3 (OUT)

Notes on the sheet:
Note: Connect J7 to program Flash
For Flash Programming (Master Configuration)
Extra Pins
For iCE Programming (Slave Configuration)
